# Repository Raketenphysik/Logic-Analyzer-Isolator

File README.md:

**WARNING: This is not a serious electronic design!**

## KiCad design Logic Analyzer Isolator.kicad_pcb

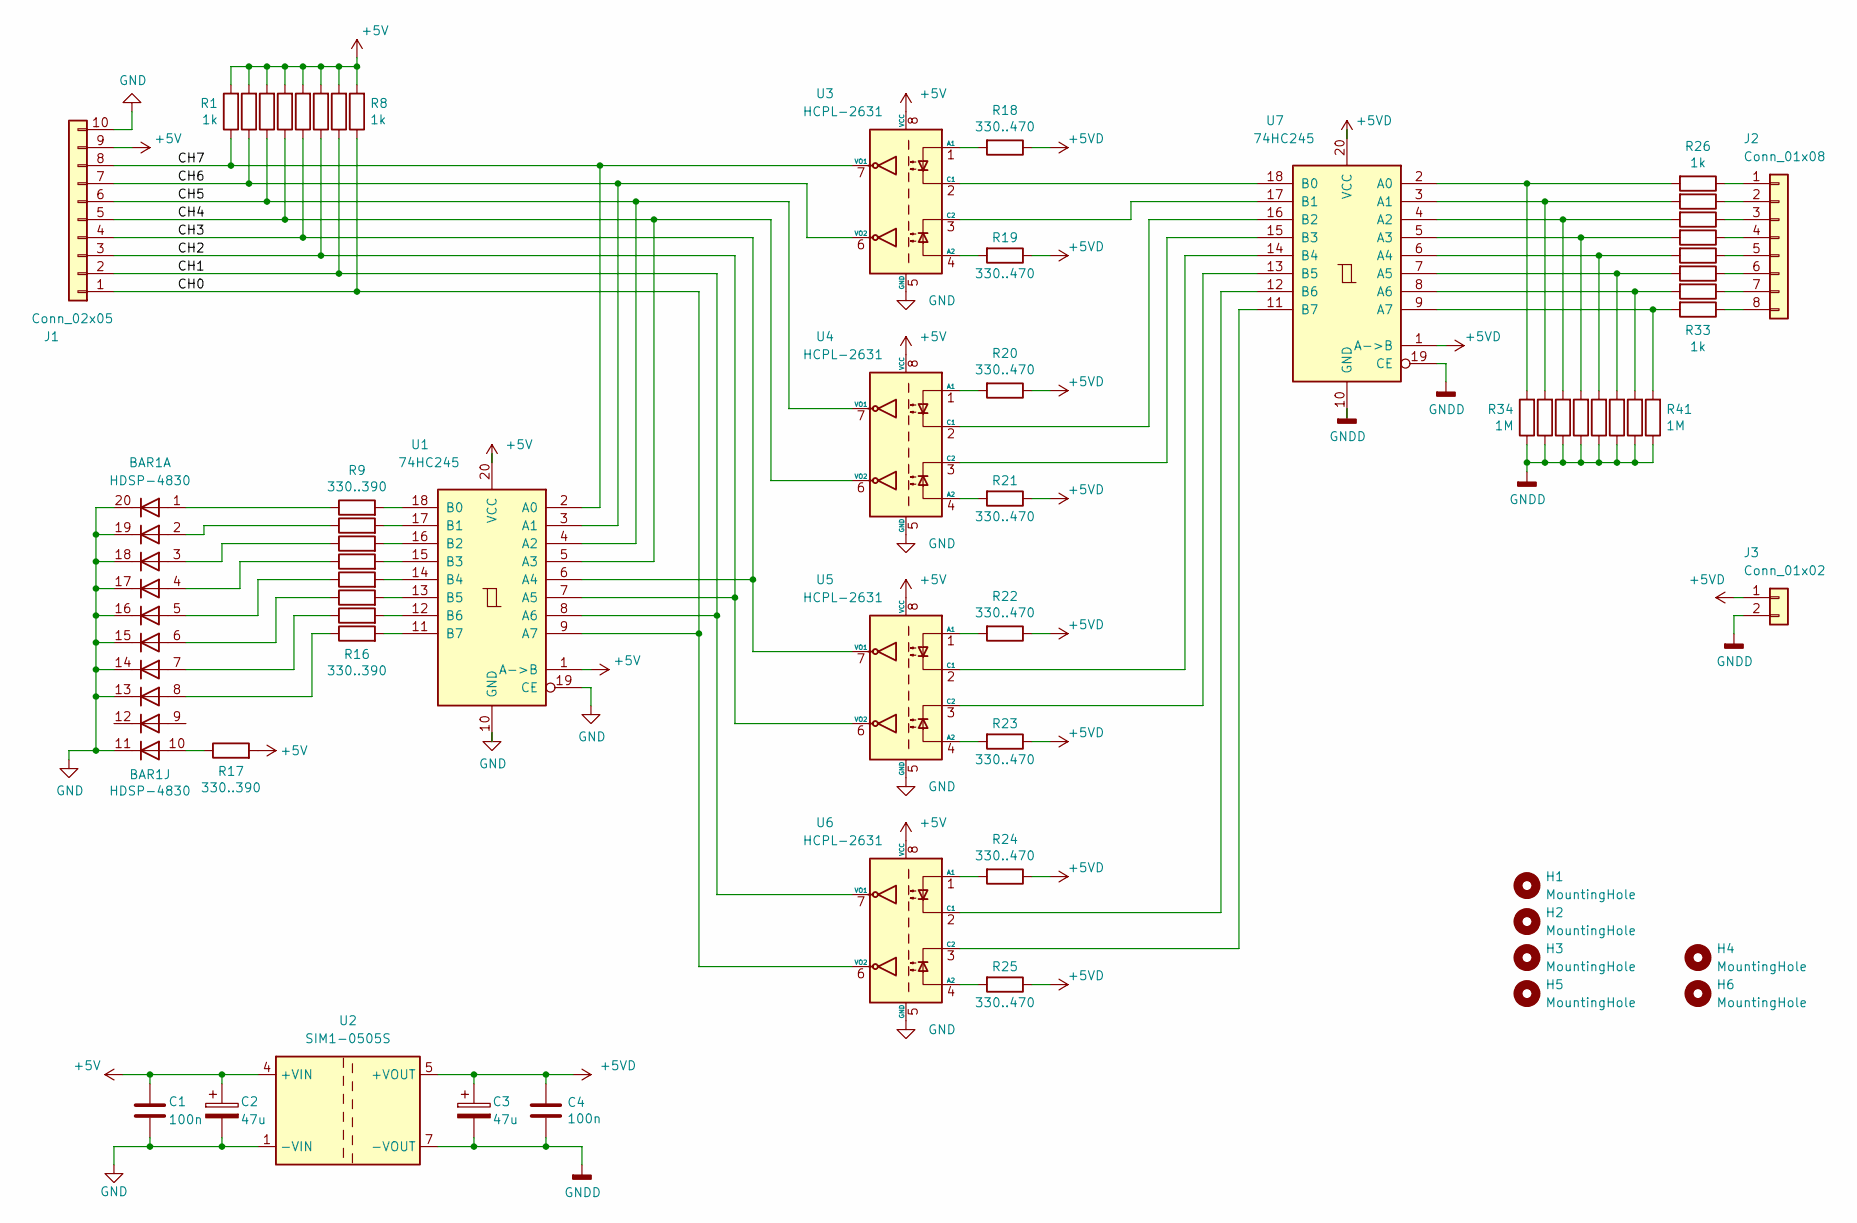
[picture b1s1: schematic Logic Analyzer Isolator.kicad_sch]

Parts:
BAR1: HDSP-4830
C1, C4: 100n; C_Disc_D4.3mm_W1.9mm_P5.00mm
C2, C3: 47u; CP_Radial_D5.0mm_P2.00mm
H1, H2, H3, H4, H5, H6: MountingHole; MountingHole_2.7mm_M2.5
J1: Conn_02x05; PinSocket_2x05_P2.54mm_Horizontal
J2: Conn_01x08; TerminalBlock_Phoenix_PT-1,5-8-3.5-H_1x08_P3.50mm_Horizontal
J3: Conn_01x02; TerminalBlock_Phoenix_PT-1,5-2-3.5-H_1x02_P3.50mm_Horizontal
R1, R2, R3, R4, R5, R6, R7, R8, R26, R27, R28, R29, R30, R31, R32, R33: 1k; R_Axial_DIN0207_L6.3mm_D2.5mm_P10.16mm_Horizontal
R9, R10, R11, R12, R13, R14, R15, R16, R17: 330..390; R_Axial_DIN0207_L6.3mm_D2.5mm_P10.16mm_Horizontal
R18, R19, R20, R21, R22, R23, R24, R25: 330..470; R_Axial_DIN0207_L6.3mm_D2.5mm_P10.16mm_Horizontal
R34, R35, R36, R37, R38, R39, R40, R41: 1M; R_Axial_DIN0207_L6.3mm_D2.5mm_P10.16mm_Horizontal
U1, U7: 74HC245; DIP-20_W7.62mm_LongPads
U2: SIM1-0505S; Converter_DCDC_Murata_CRE1xxxxxxDC_THT
U3, U4, U5, U6: HCPL-2631; DIP-8_W7.62mm

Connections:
+5V: C1.1, C2.1, J1.9, R1.2, R2.2, R3.2, R4.2, R5.2, R6.2, R7.2, R8.2, R17.2, U1.1 (A->B), U1.20 (VCC), U2.4 (+VIN), U3.8 (VCC), U4.8 (VCC), U5.8 (VCC), U6.8 (VCC)
+5VD: C3.1, C4.1, J3.1, R18.1, R19.1, R20.1, R21.1, R22.1, R23.1, R24.1, R25.1, U2.5 (+VOUT), U7.1 (A->B), U7.20 (VCC)
/CH0: J1.1, R8.1, U1.9 (A7), U6.6 (VO2)
/CH1: J1.2, R7.1, U1.8 (A6), U6.7 (VO1)
/CH2: J1.3, R6.1, U1.7 (A5), U5.6 (VO2)
/CH3: J1.4, R5.1, U1.6 (A4), U5.7 (VO1)
/CH4: J1.5, R4.1, U1.5 (A3), U4.6 (VO2)
/CH5: J1.6, R3.1, U1.4 (A2), U4.7 (VO1)
/CH6: J1.7, R2.1, U1.3 (A1), U3.6 (VO2)
/CH7: J1.8, R1.1, U1.2 (A0), U3.7 (VO1)
GND: BAR1.11 (K), BAR1.13 (K), BAR1.14 (K), BAR1.15 (K), BAR1.16 (K), BAR1.17 (K), BAR1.18 (K), BAR1.19 (K), BAR1.20 (K), C1.2, C2.2, J1.10, U1.10 (GND), U1.19 (CE), U2.1 (-VIN), U3.5 (GND), U4.5 (GND), U5.5 (GND), U6.5 (GND)
GNDD: C3.2, C4.2, J3.2, R34.1, R35.1, R36.1, R37.1, R38.1, R39.1, R40.1, R41.1, U2.7 (-VOUT), U7.10 (GND), U7.19 (CE)
unnamed: BAR1.1 (A), R9.1
unnamed: BAR1.2 (A), R10.1
unnamed: BAR1.3 (A), R11.1
unnamed: BAR1.4 (A), R12.1
unnamed: BAR1.5 (A), R13.1
unnamed: BAR1.6 (A), R14.1
unnamed: BAR1.7 (A), R15.1
unnamed: BAR1.8 (A), R16.1
unnamed: BAR1.10 (A), R17.1
unnamed: J2.1, R26.1
unnamed: J2.2, R27.1
unnamed: J2.3, R28.1
unnamed: J2.4, R29.1
unnamed: J2.5, R30.1
unnamed: J2.6, R31.1
unnamed: J2.7, R32.1
unnamed: J2.8, R33.1
unnamed: R9.2, U1.18 (B0)
unnamed: R10.2, U1.17 (B1)
unnamed: R11.2, U1.16 (B2)
unnamed: R12.2, U1.15 (B3)
unnamed: R13.2, U1.14 (B4)
unnamed: R14.2, U1.13 (B5)
unnamed: R15.2, U1.12 (B6)
unnamed: R16.2, U1.11 (B7)
unnamed: R18.2, U3.1 (A1)
unnamed: R19.2, U3.4 (A2)
unnamed: R20.2, U4.1 (A1)
unnamed: R21.2, U4.4 (A2)
unnamed: R22.2, U5.1 (A1)
unnamed: R23.2, U5.4 (A2)
unnamed: R24.2, U6.1 (A1)
unnamed: R25.2, U6.4 (A2)
unnamed: R26.2, R34.2, U7.2 (A0)
unnamed: R27.2, R35.2, U7.3 (A1)
unnamed: R28.2, R36.2, U7.4 (A2)
unnamed: R29.2, R37.2, U7.5 (A3)
unnamed: R30.2, R38.2, U7.6 (A4)
unnamed: R31.2, R39.2, U7.7 (A5)
unnamed: R32.2, R40.2, U7.8 (A6)
unnamed: R33.2, R41.2, U7.9 (A7)
unnamed: U3.2 (C1), U7.18 (B0)
unnamed: U3.3 (C2), U7.17 (B1)
unnamed: U4.2 (C1), U7.16 (B2)
unnamed: U4.3 (C2), U7.15 (B3)
unnamed: U5.2 (C1), U7.14 (B4)
unnamed: U5.3 (C2), U7.13 (B5)
unnamed: U6.2 (C1), U7.12 (B6)
unnamed: U6.3 (C2), U7.11 (B7)

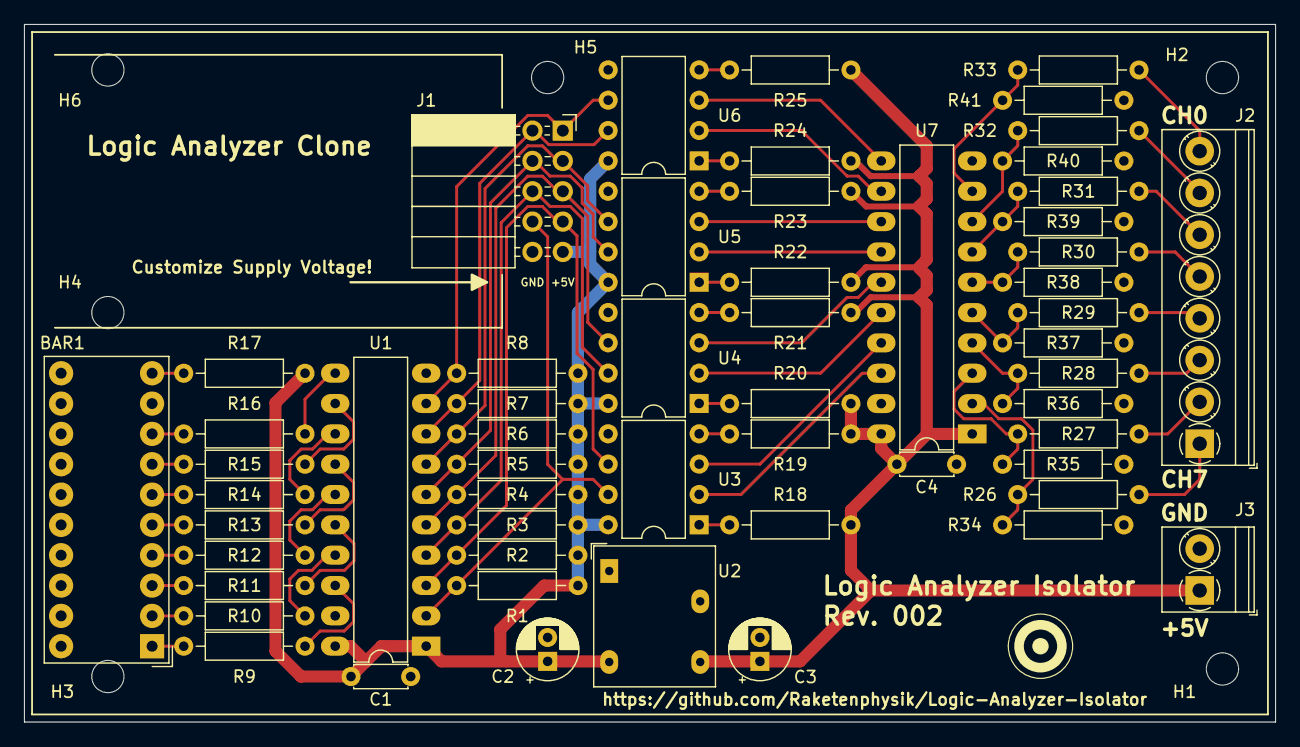
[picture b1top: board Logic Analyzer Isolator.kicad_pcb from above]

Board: 2 copper layers, 104.8 x 58.4 mm, 62 parts (0 on the bottom side), 61 nets.

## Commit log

2022-01-24 Initial commit (v002 on pcb).
2022-01-25 Added PDFs, Rendering and README. Minor changes on PCB (measurements deleted).
